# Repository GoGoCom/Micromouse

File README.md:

# Micromouse

## Introduction

Based on object-oriented theory, I redefined and systematized the Micro Mouse robot. Classes were defined, and inheritance was used to inherit characteristics from the systematized superclass. From children to elders, the robot could be modified to suit their needs, mimicking the natural behavior of an animal.

In this process, I applied the flood fill technique to capture the cerebrum instinct for direction selection, and for the cerebellum's movement, I controlled the motors with UV sensors and PIDs to mimic mouse movement. The flood fill logic was derived from the GitHub adam2392's source code, and the motor control logic was derived from the GitHub ukmars's source code, both modified to fit the intended purpose.

After production, I had to check the maze search algorithm, and I was able to do so using the maze simulation on GitHub mms and maze files. 
###  16x16 Classic size

###  32x32 Half size

## Mouses by generation

## Physical Mouse robot

I implemented the hardware using the STM32F411CEU6 Black Pill. The hardware design was created using Eagle CAD. 
Lidar sensor is option to measure a distace of front wall.

## Simulation for Teensy 4.0 (400 Mhz) 

I ran a simulation using the 400MHz Teensy 4.0 board, using the same concept applied to the STM32. It was amazing.
Move the MouseModules module in the directory to the Arduino library for use.
The mouse speed in the simulation needs an API to adjust based on the distance moved. Currently, the speed is automatically adjusted. This can be done by utilizing the forked mms source.
I'm making a mouse using the Teensy 4.0 board, so I'll show you how it turns out.

[Simulation Video](https://youtu.be/x_-rr58b5PM)
 
## Usage

* BodyConfig.h

This is where you set information related to the mouse body, such as the mouse size, wheel size, motor, sensor, encoder, etc.

| Description |
|-|
| const float WHEEL_DIAMETER = 32.0f; // Adjust on test |
| const float ENCODER_PULSES = 12.0f; // DC Motor       |
| const float GEAR_RATIO     = 51.45f; //               |
| SensorCfg;|
| MotorCfg;|

* BrainConfig.h

This is where you set information related to the mouse's brain, such as the size of the maze, the location of the goal, etc. You can also choose whether or not to simulate.
 
| Description |
|-|
| #define SIMULATION  1 // 0 or 1 - simulation or not |
||
| #define SIZE 16	// classic Size |
| #define GoalRight  SIZE/2  // center |
| #define GoalUpper  SIZE/2 |
||
|#define SIZE 32		// Half Size |
|#define GoalRight   20  // 2024 Japan |
|#define GoalUpper   9 |

* Buffers.h

This is where the size of the stack and queue is determined based on the size of the maze

| Description |
|-|
| #define STACKSIZE 8192 |
| #define QUEUESIZE 512  |

* main.cpp

Generation-specific mice are pre-prepared and available for use upon request.

| Description |
|-|
| // Active mouse |
| //BabyMouse      *mice =  &BDavid; |
| //YoungMouse     *mice =  &YDavid; |
| AdultMouse     *mice =  &ADavid; |
| //OldMouse       *mice =  &ODavid; |
| //YoungAdultMouse  *mice =  &NDavid; |

## Software tools
| Tool | version | description |
|-|-|-|
| STM32CubeIDE | 1.19.0 | software |
| Arduino IDE | 2.3.7 | software |
| QT Creator | 17.0.2 | simulation |
| Autodesk Eagle | 9.6.2 | hardware |

## Acknowledgments

I would like to thank to Adam Li of adam2392, Peter Harrison of micromouseonline and Mack of mackorone for their contributions.

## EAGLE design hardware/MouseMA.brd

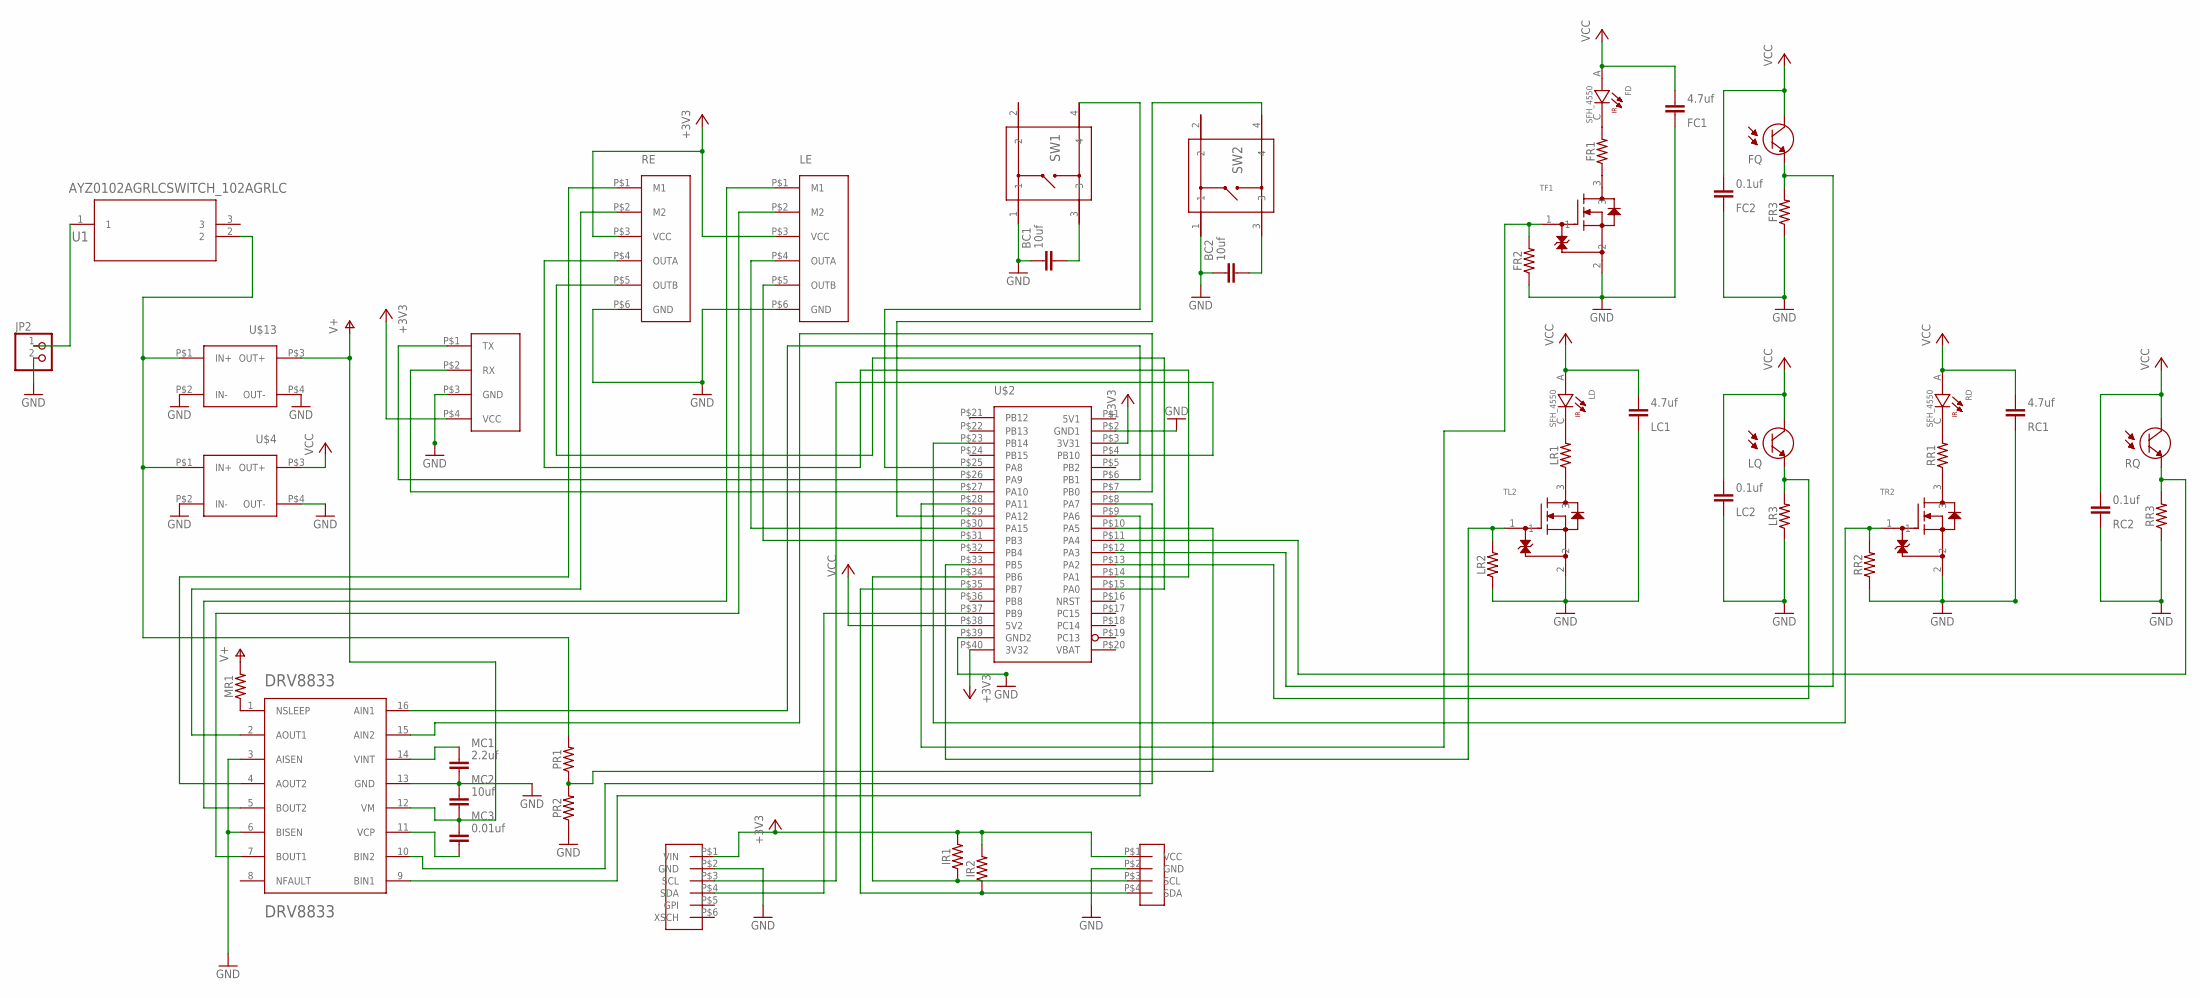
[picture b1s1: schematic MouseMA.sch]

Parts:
BC1, BC2: 10uf; C805
DRV8833PWP1: DRV8833; SOP65P640X120-17N
FC1: 4.7uf; C805
FC2: 0.1uf; C805
FD: SFH_4550; DIO_SFH_4550
FQ: TEFT4300; XDCR_TEFT4300
FR1, FR2, FR3: 0805
IR1, IR2: 2.0k; 0805
JP2: PINHD-1X2; 1X02
LC1: 4.7uf; C805
LC2: 0.1uf; C805
LD: SFH_4550; DIO_SFH_4550
LE: ENCODER; 6PINS
LQ: TEFT4300; XDCR_TEFT4300
LR1, LR2, LR3: 0805
MC1: 2.2uf; C805
MC2: 10uf; C805
MC3: 0.01uf; C805
MR1: 0805
PR1: 18K; 0805
PR2: 10k; 0805
RC1: 4.7uf; C805
RC2: 0.1uf; C805
RD: SFH_4550; DIO_SFH_4550
RE: ENCODER; 6PINS
RQ: TEFT4300; XDCR_TEFT4300
RR1, RR2, RR3: 0805
SW1, SW2: PTS815_SJM_250_SMTR_LFSSW4_PTS815_SJM_250_SMTR_LF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; SW4_PTS815_SJM_250_SMTR_LFS_CN
TF1: SSM3K324R,LFSOT-23F_TOS; SOT-23F_TOS
TL2: SSM3K324R,LFSOT-23F_TOS; SOT-23F_TOS
TR2: SSM3K324R,LFSOT-23F_TOS; SOT-23F_TOS
U1: AYZ0102AGRLCSWITCH_102AGRLC; SWITCH_102AGRLC
U$1: LADAR6DEV; 6PINS
U$2: STM32F4BOARD; STM32BOARD
U$3: OLEDVCC; OLEPINS
U$4, U$13: POWER1; PWR1PINS
UARTXRX: UART2; 4PINS

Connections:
5V1: U$2.P$1 (5V1)
+3V3: IR1.2, IR2.2, LE.P$3 (VCC), RE.P$3 (VCC), U$1.P$1 (VIN), U$2.P$3 (3V31), U$2.P$40 (3V32), U$3.P$1 (VCC), UARTXRX.P$4 (VCC)
GND: BC1.1, BC2.1, DRV8833PWP1.3 (AISEN), DRV8833PWP1.6 (BISEN), DRV8833PWP1.13 (GND), FC1.2, FC2.2, FR2.1, FR3.1, JP2.2, LC1.2, LC2.2, LE.P$6 (GND), LR2.1, LR3.1, MC1.2, MC2.1, PR2.1, RC1.2, RC2.2, RE.P$6 (GND), RR2.1, RR3.1, SW1.1, SW2.1, TF1.2, TL2.2, TR2.2, U$1.P$2 (GND), U$2.P$2 (GND1), U$2.P$39 (GND2), U$3.P$2 (GND), U$4.P$2 (IN-), U$4.P$4 (OUT-), U$13.P$2 (IN-), U$13.P$4 (OUT-), UARTXRX.P$3 (GND)
unnamed: LR2.2, TL2.1, U$2.P$33 (PB5)
unnamed: JP2.1, U1.1
unnamed: BC2.2, SW2.3
unnamed: PR1.1, PR2.2, U$2.P$10 (PA5)
unnamed: U$2.P$26 (PA9), UARTXRX.P$1 (TX)
unnamed: U$1.P$3 (SCL), U$2.P$4 (PB10)
unnamed: DRV8833PWP1.10 (BIN2), U$2.P$8 (PA7)
unnamed: U$1.P$4 (SDA), U$2.P$37 (PB9)
unnamed: FR1.1, TF1.3
unnamed: LR1.1, TL2.3
unnamed: RR1.1, TR2.3
unnamed: FR2.2, TF1.1, U$2.P$28 (PA11)
unnamed: IR2.1, U$2.P$35 (PB7), U$3.P$4 (SDA)
unnamed: BC1.2, SW1.3
unnamed: IR1.1, U$2.P$34 (PB6), U$3.P$3 (SCL)
unnamed: RE.P$5 (OUTB), U$2.P$15 (PA0)
unnamed: RE.P$4 (OUTA), U$2.P$14 (PA1)
unnamed: FD.C, FR1.2
unnamed: DRV8833PWP1.2 (AOUT1), RE.P$2 (M2)
unnamed: U$2.P$27 (PA10), UARTXRX.P$2 (RX)
unnamed: DRV8833PWP1.4 (AOUT2), RE.P$1 (M1)
unnamed: PR1.2, U1.2, U$4.P$1 (IN+), U$13.P$1 (IN+)
unnamed: DRV8833PWP1.9 (BIN1), U$2.P$9 (PA6)
unnamed: DRV8833PWP1.16 (AIN1), U$2.P$6 (PB1)
unnamed: DRV8833PWP1.7 (BOUT1), LE.P$2 (M2)
unnamed: DRV8833PWP1.5 (BOUT2), LE.P$1 (M1)
unnamed: LE.P$5 (OUTB), U$2.P$31 (PB3)
unnamed: LE.P$4 (OUTA), U$2.P$30 (PA15)
unnamed: DRV8833PWP1.1 (NSLEEP), MR1.1
unnamed: SW2.4, U$2.P$29 (PA12)
unnamed: DRV8833PWP1.14 (VINT), MC1.1
unnamed: DRV8833PWP1.11 (VCP), MC3.2
unnamed: DRV8833PWP1.15 (AIN2), U$2.P$7 (PB0)
unnamed: FQ.E, FR3.2, U$2.P$12 (PA3)
unnamed: RQ.E, RR3.2, U$2.P$11 (PA4)
unnamed: LQ.E, LR3.2, U$2.P$13 (PA2)
unnamed: SW1.4, U$2.P$25 (PA8)
unnamed: LD.C, LR1.2
unnamed: RD.C, RR1.2
unnamed: RR2.2, TR2.1, U$2.P$23 (PB14)
V+: DRV8833PWP1.12 (VM), MC2.2, MC3.1, MR1.2, U$13.P$3 (OUT+)
VBAT: U$2.P$20 (VBAT)
VCC: FC1.1, FC2.1, FD.A, FQ.C, LC1.1, LC2.1, LD.A, LQ.C, RC1.1, RC2.1, RD.A, RQ.C, U$2.P$38 (5V2), U$4.P$3 (OUT+)

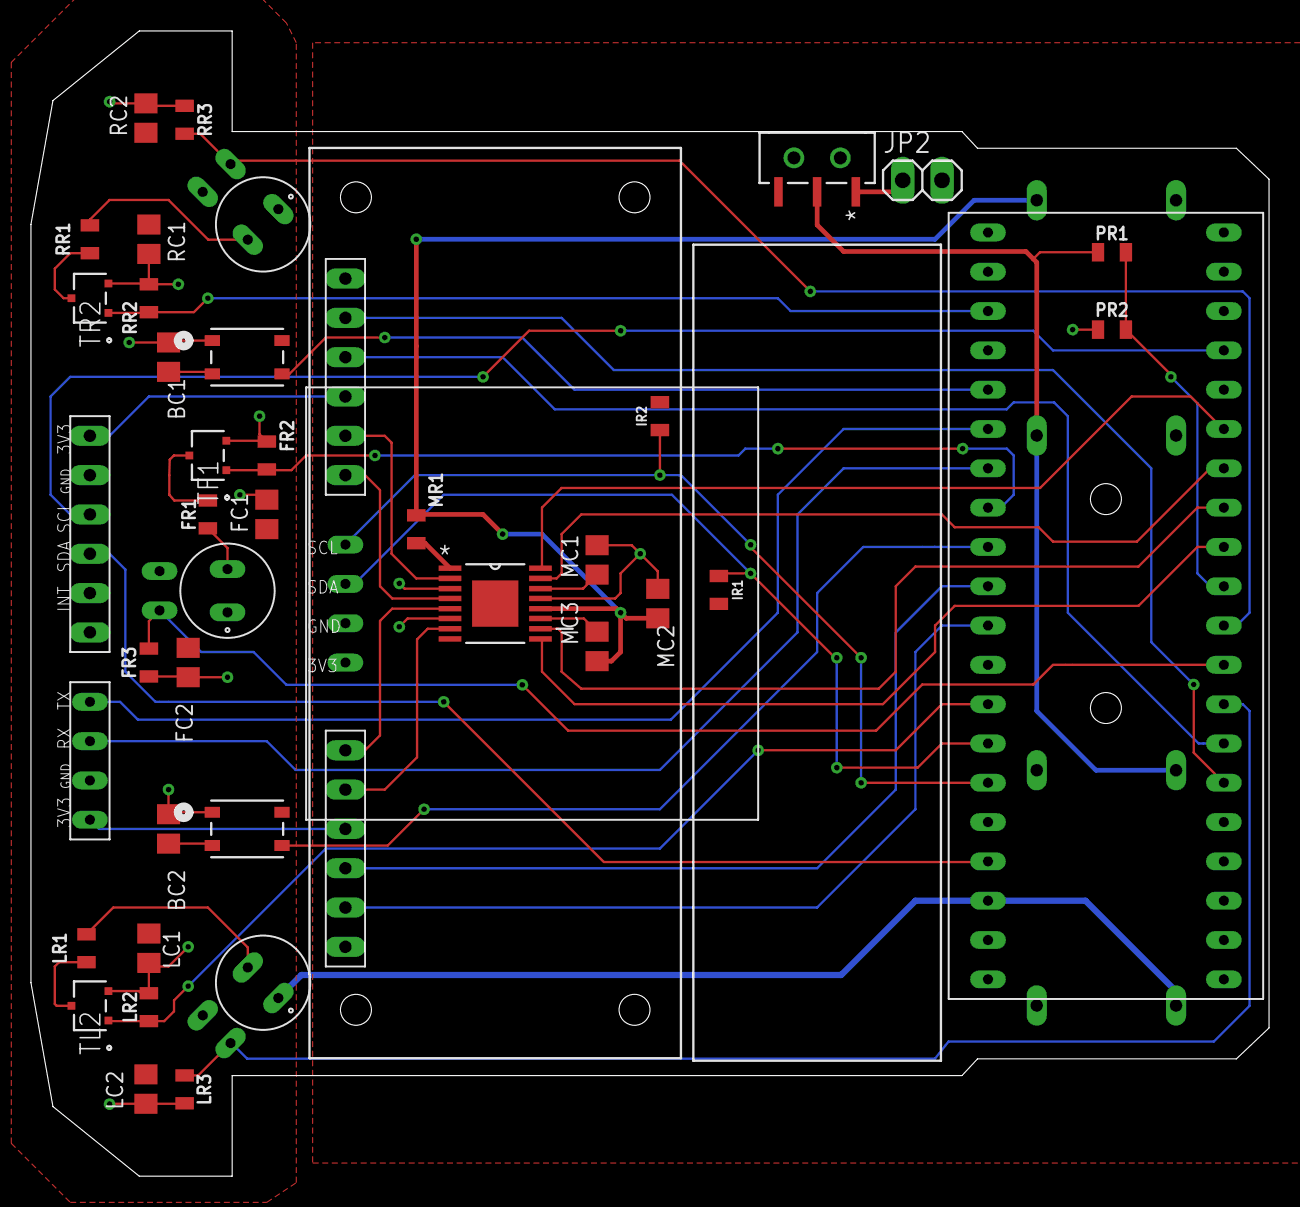
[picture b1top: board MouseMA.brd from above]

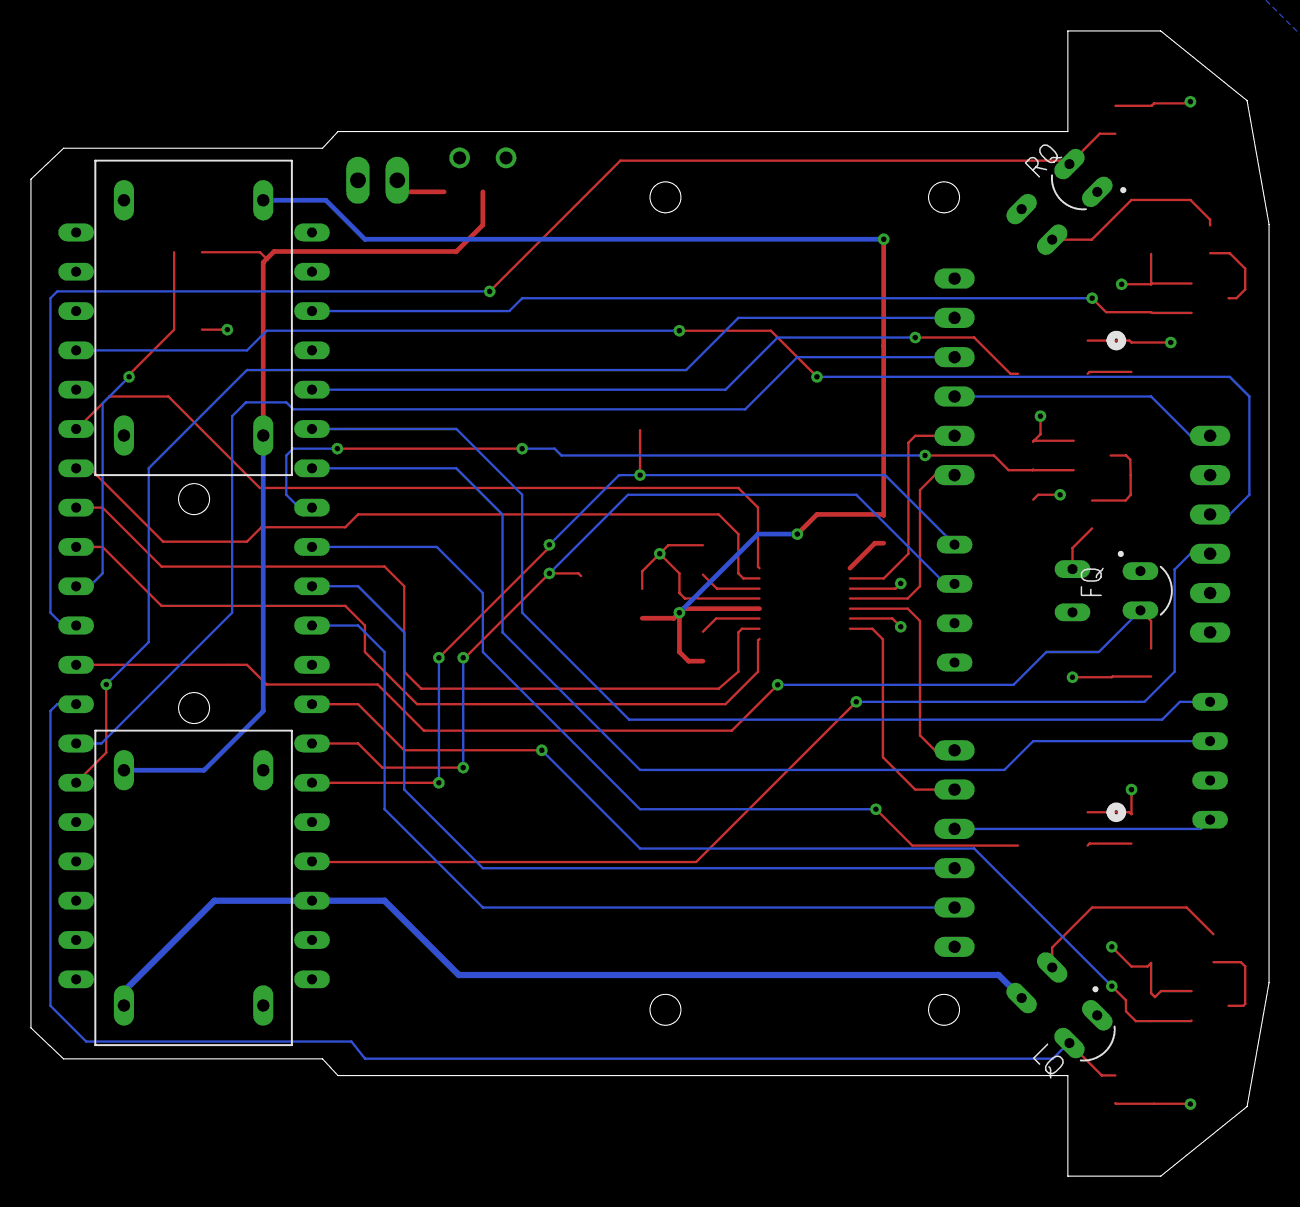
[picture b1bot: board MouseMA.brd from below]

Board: 2 copper layers, 80.0 x 74.0 mm, 47 parts (5 on the bottom side), 44 nets.

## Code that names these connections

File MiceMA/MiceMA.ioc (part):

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Mcu.Name=STM32F411C(C-E)Ux
Mcu.Package=UFQFPN48
Mcu.UserName=STM32F411CEUx
PA0-WKUP.Signal=S_TIM5_CH1
PA1.Signal=S_TIM5_CH2
PA10.Mode=Asynchronous
PA10.Signal=USART1_RX
PA11.GPIOParameters=GPIO_Label
PA11.GPIO_Label=FEYE
PA11.Signal=GPIO_Output
PA12.GPIOParameters=GPIO_PuPd,GPIO_Label
PA12.GPIO_Label=USRBTN2
PA12.GPIO_PuPd=GPIO_PULLUP
PA12.Signal=GPIO_Input
PA15.Signal=S_TIM2_CH1_ETR
PA2.GPIOParameters=GPIO_Label
PA2.GPIO_Label=LEYEV
PA2.Signal=ADCx_IN2
PA3.GPIOParameters=GPIO_Label
PA3.GPIO_Label=FEYEV
PA3.Signal=ADCx_IN3
PA4.GPIOParameters=GPIO_Label
PA4.GPIO_Label=REYEV
PA4.Signal=ADCx_IN4
PA5.GPIOParameters=GPIO_Label
PA5.GPIO_Label=MOTBAT
PA5.Signal=ADCx_IN5
PA6.Signal=S_TIM3_CH1
PA7.Signal=S_TIM3_CH2
PA8.GPIOParameters=GPIO_PuPd,GPIO_Label
PA8.GPIO_Label=USRBTN1
PA8.GPIO_PuPd=GPIO_PULLUP
PA8.Signal=GPIO_Input
PA9.Mode=Asynchronous
PA9.Signal=USART1_TX
PB0.Signal=S_TIM3_CH3
PB1.Signal=S_TIM3_CH4
PB14.GPIOParameters=GPIO_Label
PB14.GPIO_Label=REYE
PB14.Signal=GPIO_Output
PB3.Signal=S_TIM2_CH2
PB5.GPIOParameters=GPIO_Label
PB5.GPIO_Label=LEYE
PB5.Signal=GPIO_Output
PB6.Mode=I2C
PB6.Signal=I2C1_SCL
PB7.Mode=I2C
PB7.Signal=I2C1_SDA
PC13-ANTI_TAMP.GPIOParameters=GPIO_Label
PC13-ANTI_TAMP.GPIO_Label=SYSLED
PC13-ANTI_TAMP.Signal=GPIO_Output
PH0\ -\ OSC_IN.Mode=HSE-External-Oscillator
PH0\ -\ OSC_IN.Signal=RCC_OSC_IN
PH1\ -\ OSC_OUT.Mode=HSE-External-Oscillator
PH1\ -\ OSC_OUT.Signal=RCC_OSC_OUT
RCC.HSE_VALUE=25000000
RCC.SYSCLKFreq_VALUE=100000000
RCC.SYSCLKSource=RCC_SYSCLKSOURCE_PLLCLK
board=custom

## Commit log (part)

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2026-01-11 upload
2026-01-11 change
2026-01-12 upload new photo
2026-01-12 upload new file
2026-01-12 change a little
2026-01-12 upload software
2026-01-13 optimize path bug
2026-01-30 Teensy40 upload

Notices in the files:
parts and their libraries:
SparkFun-Resistors: Licensing: Creative Commons ShareAlike 4.0 International - https://creativecommons.org/licenses/by-sa/4.0
COPYRIGHT: Copyright (C) 2024 Ultra Librarian. All rights reserved.
